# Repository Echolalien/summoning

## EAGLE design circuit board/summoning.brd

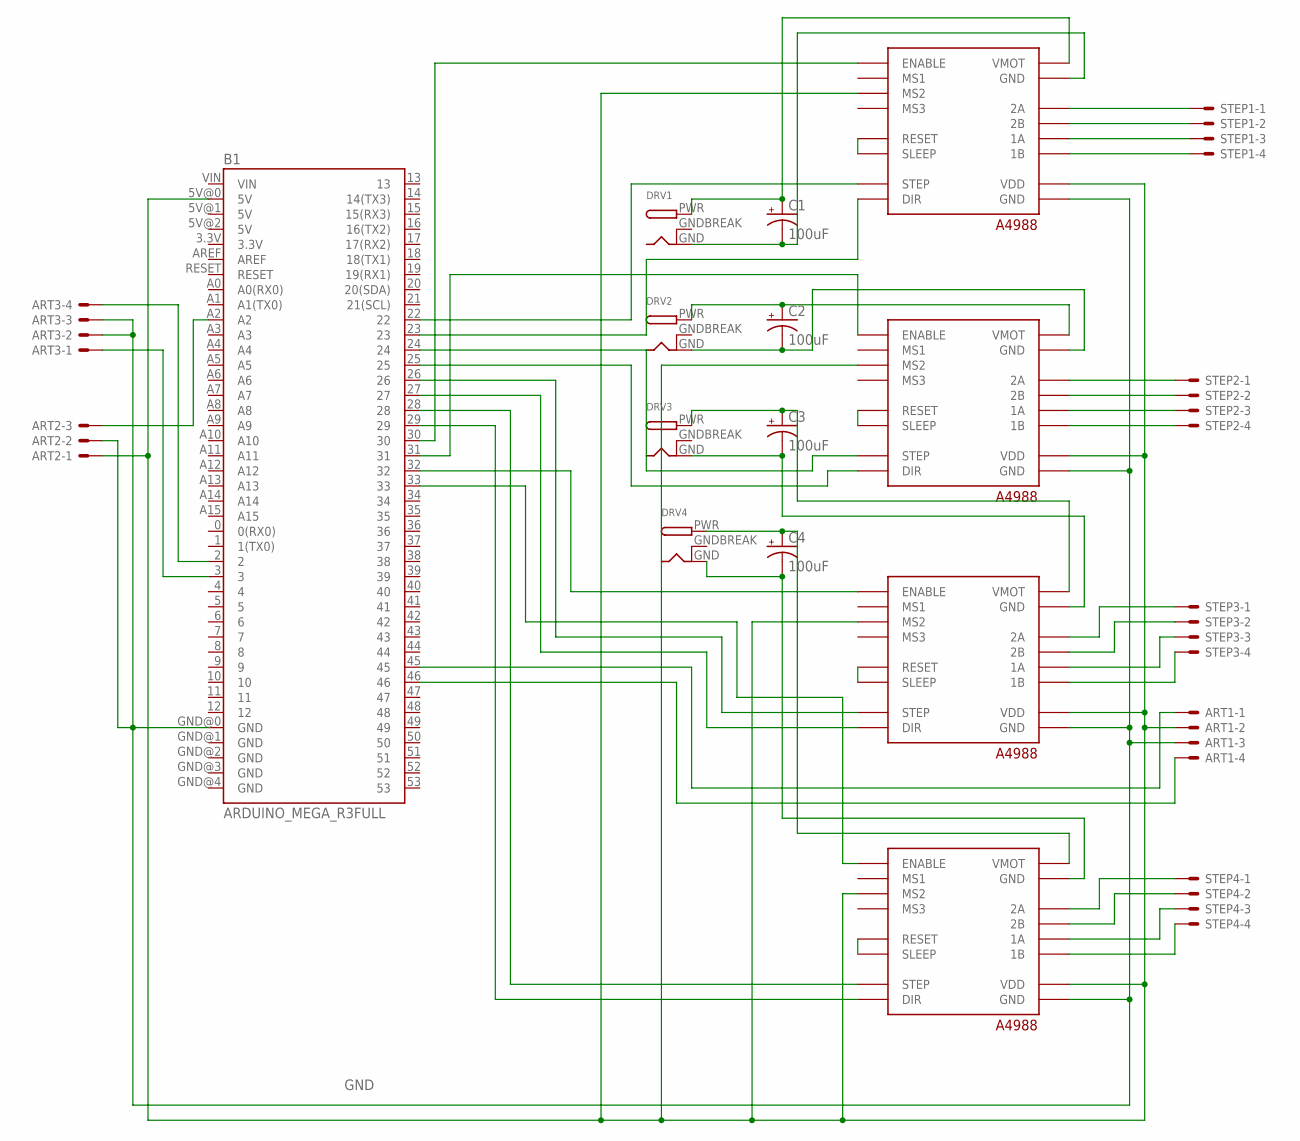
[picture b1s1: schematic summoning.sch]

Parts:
ART1, ART3: KK-156-4
ART2: KK-156-3
B1: ARDUINO_MEGA_R3FULL; ARDUINO_MEGA
C1, C2, C3, C4: 100uF; CPOL-RADIAL-2.5MM-6.5MM
DRV1, DRV2, DRV3, DRV4: DCBARRELPTH; DCJACK_2MM_PTH
POL1, POL2, POL3, POL4: A4988_ALL
STEP1, STEP2, STEP3, STEP4: KK-156-4

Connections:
GND: ART1.3, ART2.2, ART3.2, ART3.3, B1.GND@0 (GND), POL1.P16 (GND), POL2.P16 (GND), POL3.P16 (GND), POL4.P16 (GND)
GNDBREAK: DRV1.GNDBREAK, DRV2.GNDBREAK, DRV3.GNDBREAK, DRV4.GNDBREAK
unnamed: ART1.2, ART2.1, B1.5V@0 (5V), POL1.P3 (MS2), POL1.P15 (VDD), POL2.P3 (MS2), POL2.P15 (VDD), POL3.P3 (MS2), POL3.P15 (VDD), POL4.P3 (MS2), POL4.P15 (VDD)
unnamed: C4.2 (-), DRV4.GND, POL4.P10 (GND)
unnamed: C4.1 (+), DRV4.PWR, POL4.P9 (VMOT)
unnamed: C3.1 (+), DRV3.PWR, POL3.P9 (VMOT)
unnamed: C3.2 (-), DRV3.GND, POL3.P10 (GND)
unnamed: C2.2 (-), DRV2.GND, POL2.P10 (GND)
unnamed: C2.1 (+), DRV2.PWR, POL2.P9 (VMOT)
unnamed: C1.2 (-), DRV1.GND, POL1.P10 (GND)
unnamed: C1.1 (+), DRV1.PWR, POL1.P9 (VMOT)
unnamed: POL1.P11 (2A), STEP1.1
unnamed: POL1.P12 (2B), STEP1.2
unnamed: POL1.P13 (1A), STEP1.3
unnamed: POL1.P14 (1B), STEP1.4
unnamed: POL2.P11 (2A), STEP2.1
unnamed: POL2.P12 (2B), STEP2.2
unnamed: POL2.P13 (1A), STEP2.3
unnamed: POL2.P14 (1B), STEP2.4
unnamed: POL3.P11 (2A), STEP3.1
unnamed: POL3.P12 (2B), STEP3.2
unnamed: POL3.P13 (1A), STEP3.3
unnamed: POL3.P14 (1B), STEP3.4
unnamed: POL4.P11 (2A), STEP4.1
unnamed: POL4.P12 (2B), STEP4.2
unnamed: POL4.P13 (1A), STEP4.3
unnamed: POL4.P14 (1B), STEP4.4
unnamed: B1.27, POL3.P8 (DIR)
unnamed: B1.26, POL3.P7 (STEP)
unnamed: ART2.3, B1.A2
unnamed: ART3.4, B1.2
unnamed: ART3.1, B1.3
unnamed: ART1.1, B1.45
unnamed: ART1.4, B1.46
unnamed: B1.30, POL1.P1 (ENABLE)
unnamed: B1.22, POL1.P7 (STEP)
unnamed: B1.23, POL1.P8 (DIR)
unnamed: B1.24, POL2.P7 (STEP)
unnamed: B1.25, POL2.P8 (DIR)
unnamed: B1.28, POL4.P7 (STEP)
unnamed: B1.29, POL4.P8 (DIR)
unnamed: B1.31, POL2.P1 (ENABLE)
unnamed: B1.32, POL3.P1 (ENABLE)
unnamed: B1.33, POL4.P1 (ENABLE)
unnamed: POL1.P5 (RESET), POL1.P6 (SLEEP)
unnamed: POL2.P5 (RESET), POL2.P6 (SLEEP)
unnamed: POL3.P5 (RESET), POL3.P6 (SLEEP)
unnamed: POL4.P5 (RESET), POL4.P6 (SLEEP)

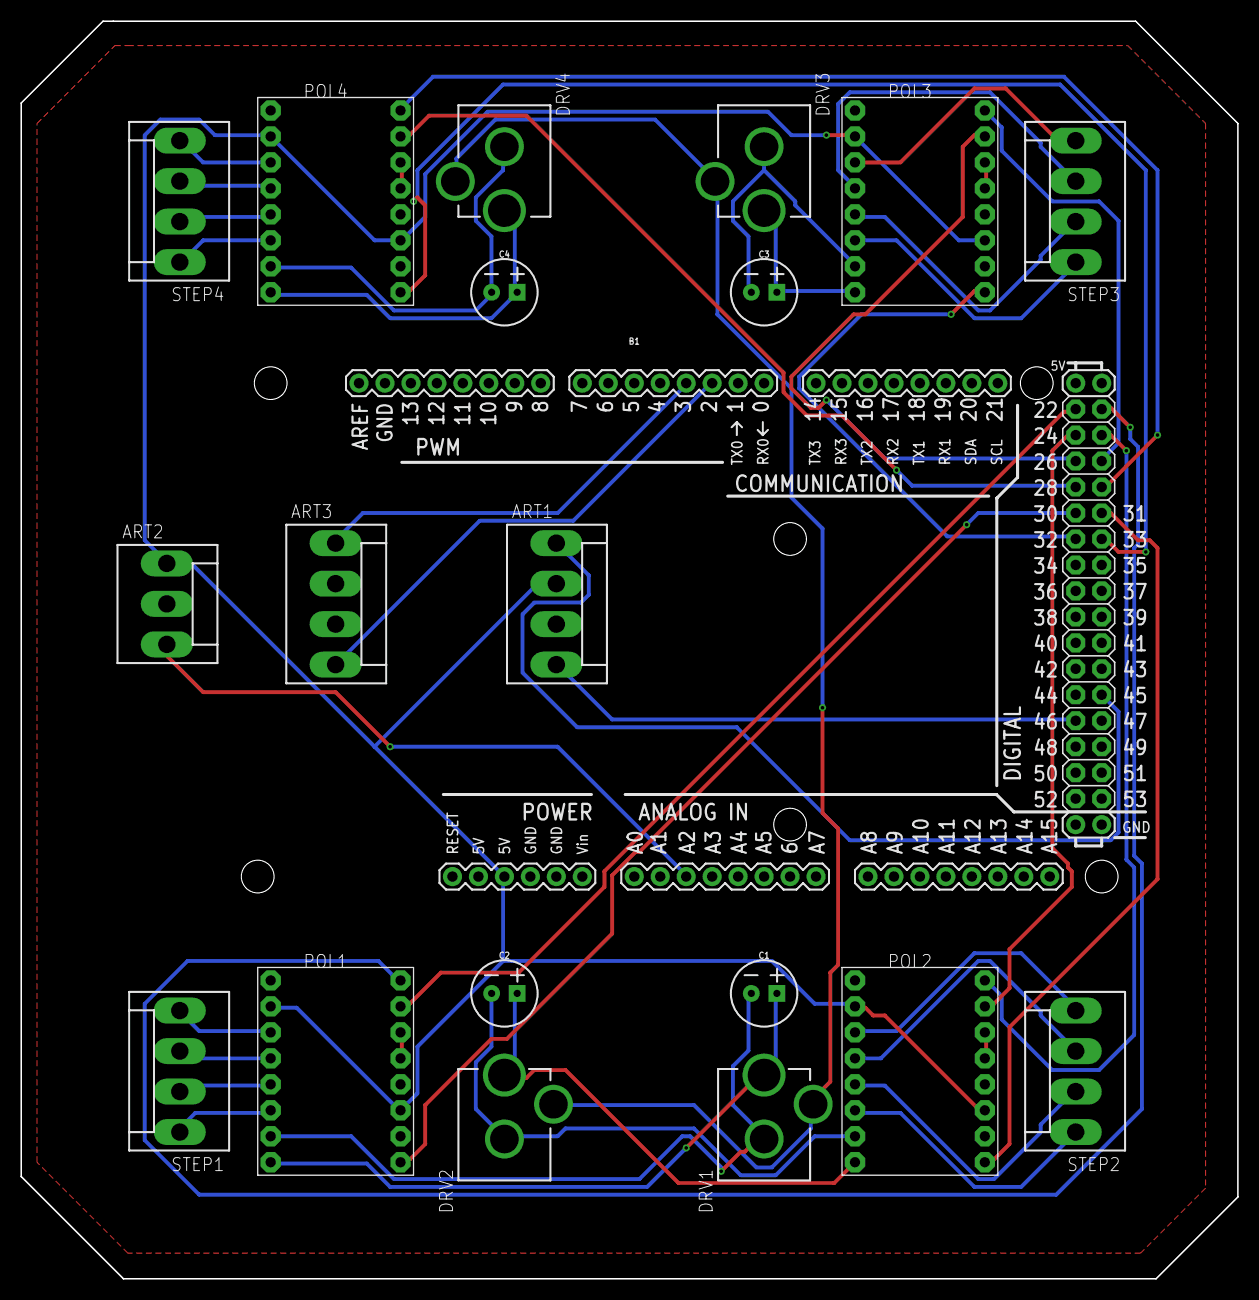
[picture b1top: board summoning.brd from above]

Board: 2 copper layers, 119.0 x 123.0 mm, 20 parts (0 on the bottom side), 48 nets.

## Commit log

2019-08-07 adding oF sketch
2019-08-07 adding arduino firmware v1
2019-08-07 file structure change arduino
2019-08-07 code restructure, ready for control code, safety check and calibration code complete
2019-08-08 manual control in place! safety code working, needs calibrating
2019-08-09 yaw working, tests and calibration work well, maybe want to change how endstop is handled
2019-09-03 tip roll clibration done, god knows what else
2019-09-03 drum roll calibration lazily copied from tip roll, all tip roll variables now use tip instead of roll as reference
2019-09-03 roll knob controls implemented. general tidy up
2019-09-05 adding circuit board files
2019-09-05 adding 3d print files and design
2019-09-05 accepted that tip roll orientation sensor has broken off inside top articulation. not worth fixing at this stage. robot will now arbitrarily cock her head at people. calibration no longer necessary a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

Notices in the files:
parts and their libraries:
SparkFun-Capacitors: Licensing: Creative Commons ShareAlike 4.0 International - https://creativecommons.org/licenses/by-sa/4.0
